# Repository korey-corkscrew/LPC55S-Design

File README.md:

# LPC55S-Design
## Flexcomm Assignment

## Schematics
### MCU

### EERAM

### Camera

### TOF

### WiFi

### CAN

### USB

### JTAG

## PCB

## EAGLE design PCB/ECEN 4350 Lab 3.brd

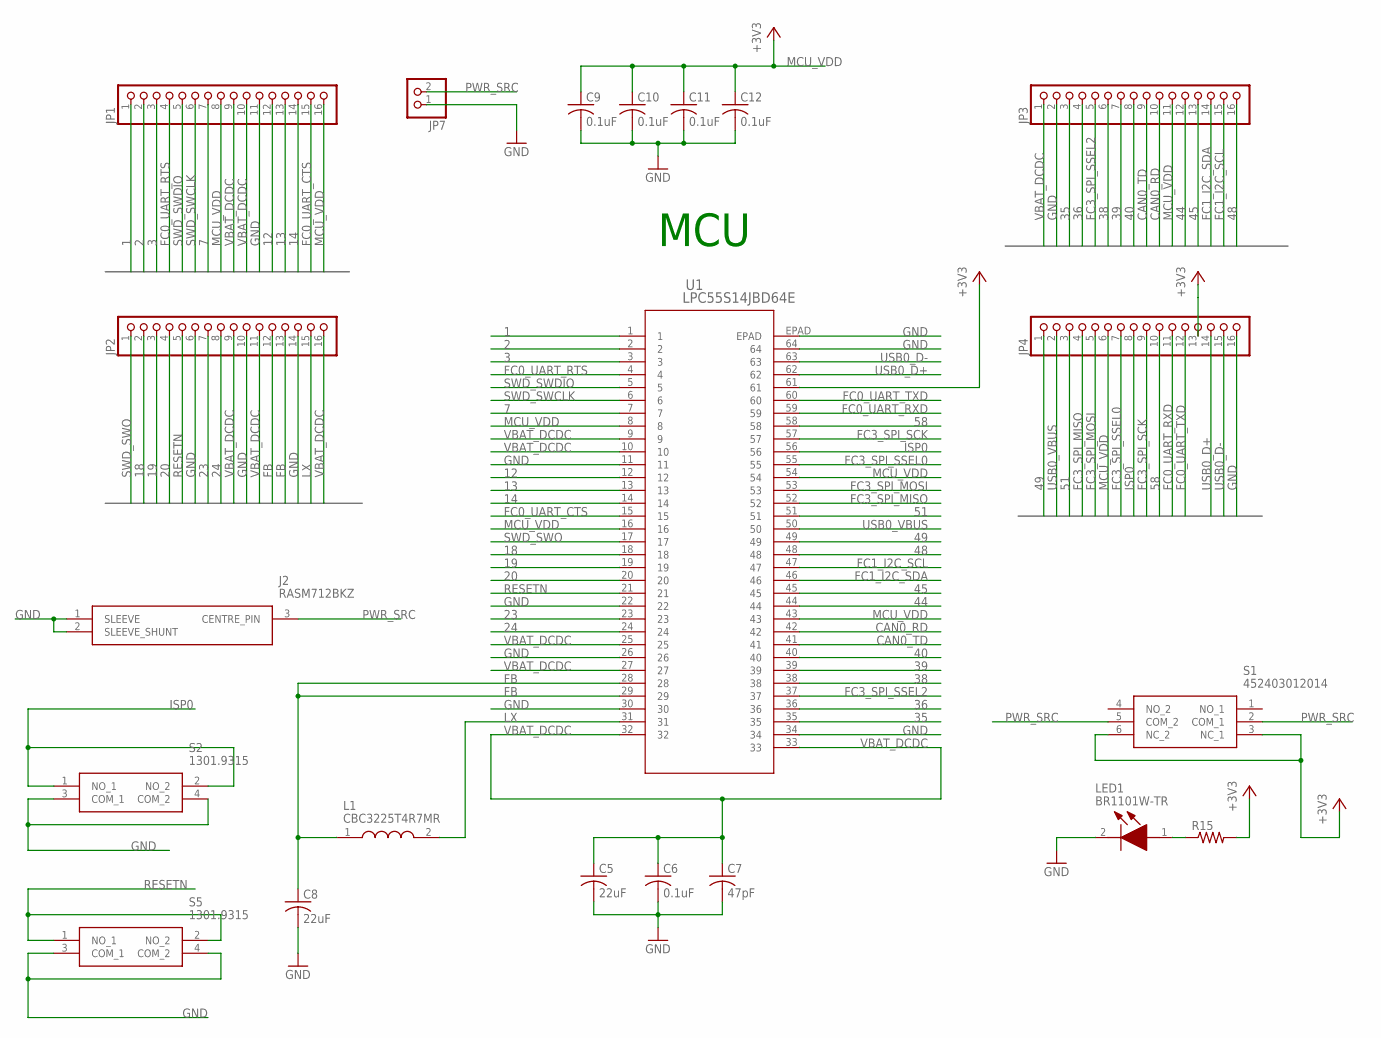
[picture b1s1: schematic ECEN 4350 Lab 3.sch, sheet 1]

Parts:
C5, C8: 22uF; C1206
C6, C9, C10, C11, C12: 0.1uF; C1206
C7: 47pF; C1206
J2: RASM712BKZ
JP1, JP2, JP3, JP4: PINHD-1X16; 1X16
JP7: PINHD-1X2; 1X02
L1: CBC3225T4R7MR; INDC3225X270N
LED1: BR1101W-TR; BR1101WTR
R15: R-US_R1206; R1206
S1: 452403012014
S2, S5: 1301.9315; 13019319
U1: LPC55S14JBD64E; HTQFP64_10X10_NXP

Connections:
1: JP1.1, U1.1
2: JP1.2, U1.2
3: JP1.3, U1.3
7: JP1.7, U1.7
12: JP1.12, U1.12
13: JP1.13, U1.13
14: JP1.14, U1.14
18: JP2.2, U1.18
19: JP2.3, U1.19
20: JP2.4, U1.20
23: JP2.7, U1.23
24: JP2.8, U1.24
35: JP3.3, U1.35
36: JP3.4, U1.36
38: JP3.6, U1.38
39: JP3.7, U1.39
40: JP3.8, U1.40
44: JP3.12, U1.44
45: JP3.13, U1.45
48: JP3.16, U1.48
49: JP4.1, U1.49
51: JP4.3, U1.51
58: JP4.10, U1.58
+3V3: R15.2, S1.3 (NC_1), S1.6 (NC_2), U1.61; also elsewhere on the board
CAN0_RD: JP3.10, U1.42; also elsewhere on the board
CAN0_TD: JP3.9, U1.41; also elsewhere on the board
FB: C8.1, JP2.12, JP2.13, L1.1, U1.28, U1.29
FC0_UART_CTS: JP1.15, U1.15
FC0_UART_RTS: JP1.4, U1.4
FC0_UART_RXD: JP4.11, U1.59; also elsewhere on the board
FC0_UART_TXD: JP4.12, U1.60; also elsewhere on the board
FC1_I2C_SCL: JP3.15, U1.47; also elsewhere on the board
FC1_I2C_SDA: JP3.14, U1.46; also elsewhere on the board
FC3_SPI_MISO: JP4.4, U1.52; also elsewhere on the board
FC3_SPI_MOSI: JP4.5, U1.53; also elsewhere on the board
FC3_SPI_SCK: JP4.9, U1.57; also elsewhere on the board
FC3_SPI_SSEL0: JP4.7, U1.55; also elsewhere on the board
FC3_SPI_SSEL2: JP3.5, U1.37; also elsewhere on the board
GND: C5.2, C6.2, C7.2, C8.2, C9.2, C10.2, C11.2, C12.2, J2.1 (SLEEVE), J2.2 (SLEEVE_SHUNT), JP1.11, JP2.6, JP2.10, JP2.14, JP3.2, JP4.16, JP7.1, LED1.2 (K), S2.3 (COM_1), S2.4 (COM_2), S5.3 (COM_1), S5.4 (COM_2), U1.11, U1.22, U1.26, U1.30, U1.34, U1.64, U1.EPAD; also elsewhere on the board
ISP0: JP4.8, S2.1 (NO_1), S2.2 (NO_2), U1.56
LX: JP2.15, L1.2, U1.31
MCU_VDD: C9.1, C10.1, C11.1, C12.1, JP1.8, JP1.16, JP3.11, JP4.6, U1.8, U1.16, U1.43, U1.54
unnamed: LED1.1 (A), R15.1
PWR_SRC: J2.3 (CENTRE_PIN), JP7.2, S1.2 (COM_1), S1.5 (COM_2)
RESETN: JP2.5, S5.1 (NO_1), S5.2 (NO_2), U1.21; also elsewhere on the board
SWD_SWCLK: JP1.6, U1.6; also elsewhere on the board
SWD_SWDIO: JP1.5, U1.5; also elsewhere on the board
SWD_SWO: JP2.1, U1.17; also elsewhere on the board
USB0_D+: JP4.14, U1.62; also elsewhere on the board
USB0_D-: JP4.15, U1.63; also elsewhere on the board
USB0_VBUS: JP4.2, U1.50; also elsewhere on the board
VBAT_DCDC: C5.1, C6.1, C7.1, JP1.9, JP1.10, JP2.9, JP2.11, JP2.16, JP3.1, U1.9, U1.10, U1.25, U1.27, U1.32, U1.33

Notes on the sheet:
MCU

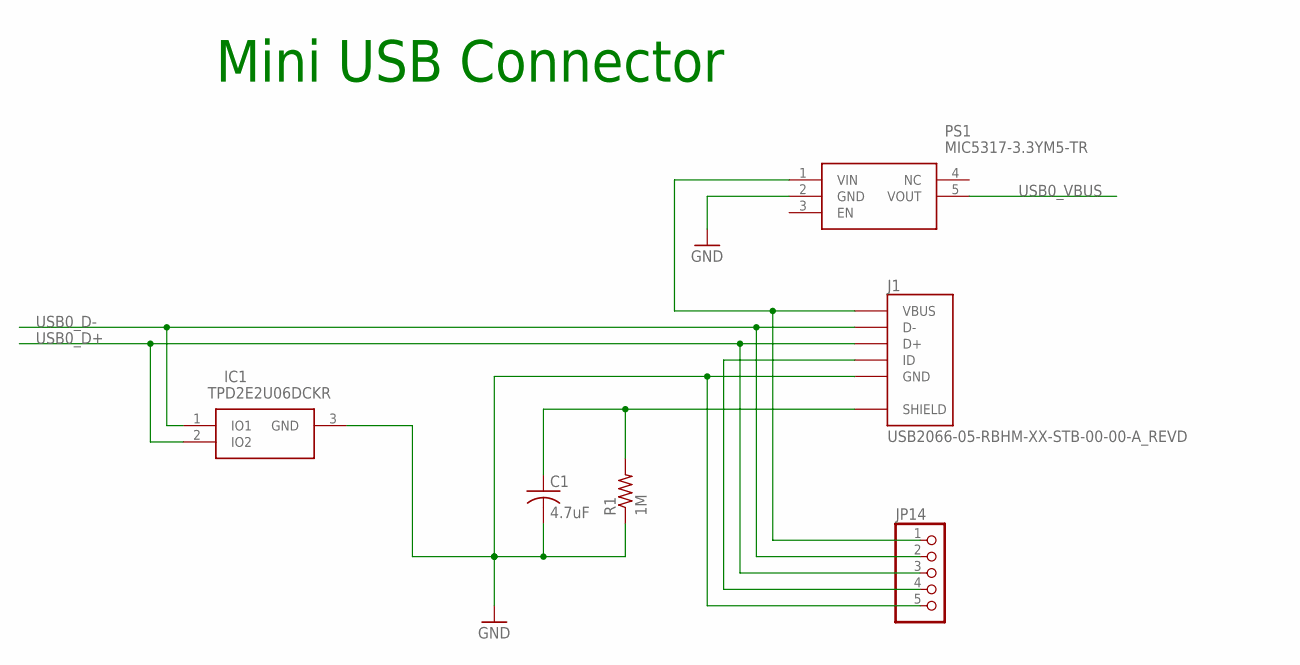
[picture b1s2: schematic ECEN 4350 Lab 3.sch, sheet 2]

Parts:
C1: 4.7uF; C1206
IC1: TPD2E2U06DCKR; SOT65P210X110-3N
J1: USB2066-05-RBHM-XX-STB-00-00-A_REVD; GCT_USB2066-05-RBHM-XX-STB-00-00-A_REVD
JP14: PINHD-1X5; 1X05
PS1: MIC5317-3.3YM5-TR; SOT95P280X100-5N
R1: 1M; R1206

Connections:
+5V: J1.1 (VBUS), JP14.1, PS1.1 (VIN)
GND: C1.2, IC1.3 (GND), J1.5 (GND), JP14.5, PS1.2 (GND), R1.1; also elsewhere on the board
unnamed: C1.1, J1.6 (SHIELD), J1.7 (SHIELD), J1.8 (SHIELD), J1.9 (SHIELD), R1.2
unnamed: J1.4 (ID), JP14.4
USB0_D+: IC1.2 (IO2), J1.3 (D+), JP14.3; also elsewhere on the board
USB0_D-: IC1.1 (IO1), J1.2 (D-), JP14.2; also elsewhere on the board
USB0_VBUS: PS1.5 (VOUT); also elsewhere on the board

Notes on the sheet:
Mini USB Connector

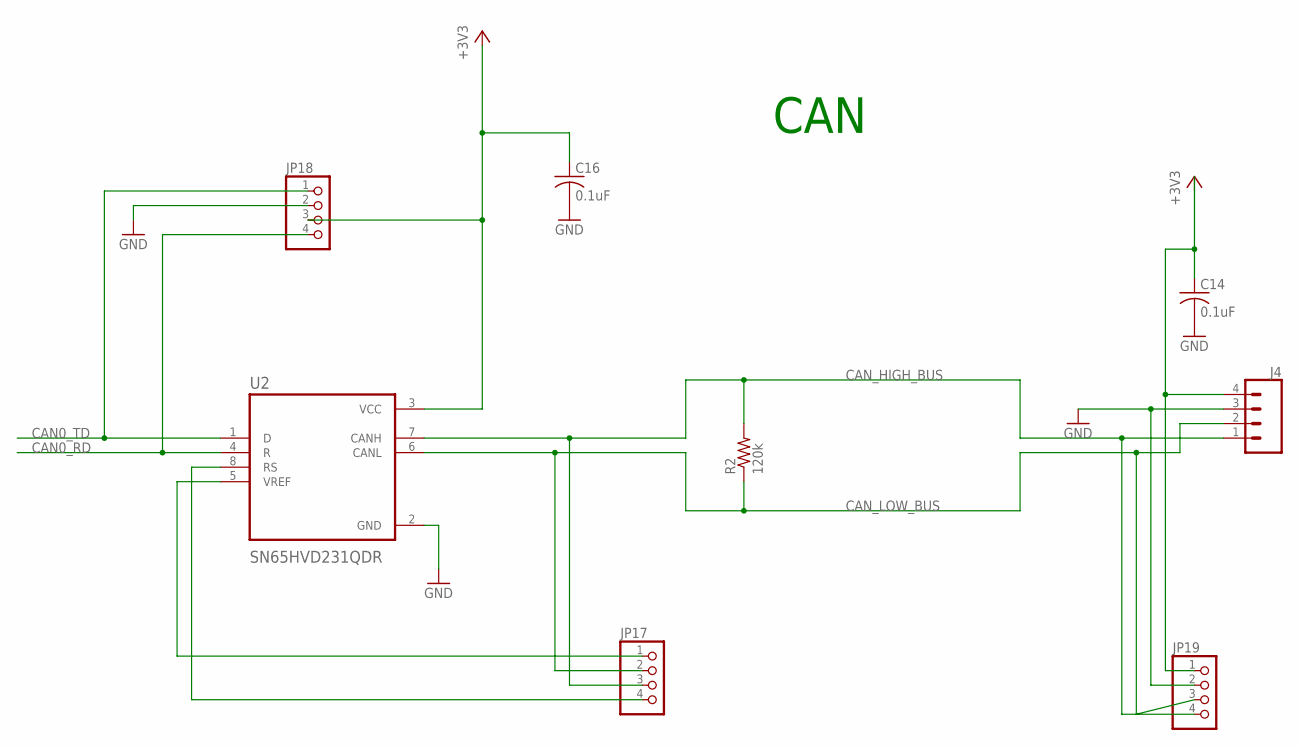
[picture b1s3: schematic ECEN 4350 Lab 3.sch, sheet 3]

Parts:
C14, C16: 0.1uF; C1206
J4: CONN_04SMD2; JST04_1MM_RA
JP17, JP18, JP19: PINHD-1X4; 1X04
R2: 120k; R1206
U2: SN65HVD231QDR; SOIC127P599X175-8N

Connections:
+3V3: C14.1, C16.1, J4.4, JP18.3, JP19.1, U2.3 (VCC); also elsewhere on the board
CAN0_RD: JP18.4, U2.4 (R); also elsewhere on the board
CAN0_TD: JP18.1, U2.1 (D); also elsewhere on the board
CAN_HIGH_BUS: J4.1, JP17.3, JP19.4, R2.2, U2.7 (CANH)
CAN_LOW_BUS: J4.2, JP17.2, JP19.3, R2.1, U2.6 (CANL)
GND: C14.2, C16.2, J4.3, JP18.2, JP19.2, U2.2 (GND); also elsewhere on the board
unnamed: JP17.4, U2.8 (RS)
unnamed: JP17.1, U2.5 (VREF)

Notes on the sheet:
CAN

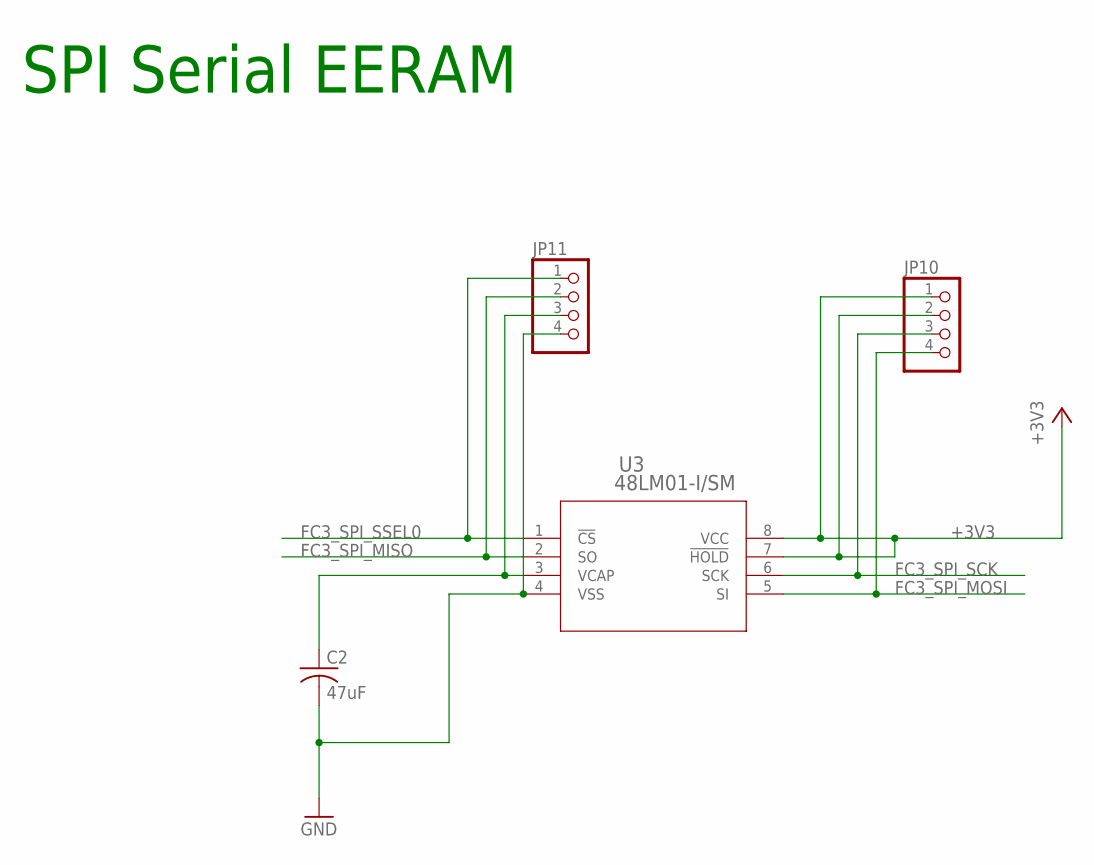
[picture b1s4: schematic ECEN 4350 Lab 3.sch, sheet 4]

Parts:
C2: 47uF; C1206
JP10, JP11: PINHD-1X4; 1X04
U3: 48LM01-I/SM; SOIJ8_SM_MCH

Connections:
+3V3: JP10.1, JP10.2, U3.7 (!HOLD), U3.8 (VCC); also elsewhere on the board
FC3_SPI_MISO: JP11.2, U3.2 (SO); also elsewhere on the board
FC3_SPI_MOSI: JP10.4, U3.5 (SI); also elsewhere on the board
FC3_SPI_SCK: JP10.3, U3.6 (SCK); also elsewhere on the board
FC3_SPI_SSEL0: JP11.1, U3.1 (!CS); also elsewhere on the board
GND: C2.2, JP11.4, U3.4 (VSS); also elsewhere on the board
unnamed: C2.1, JP11.3, U3.3 (VCAP)

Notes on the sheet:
SPI Serial EERAM

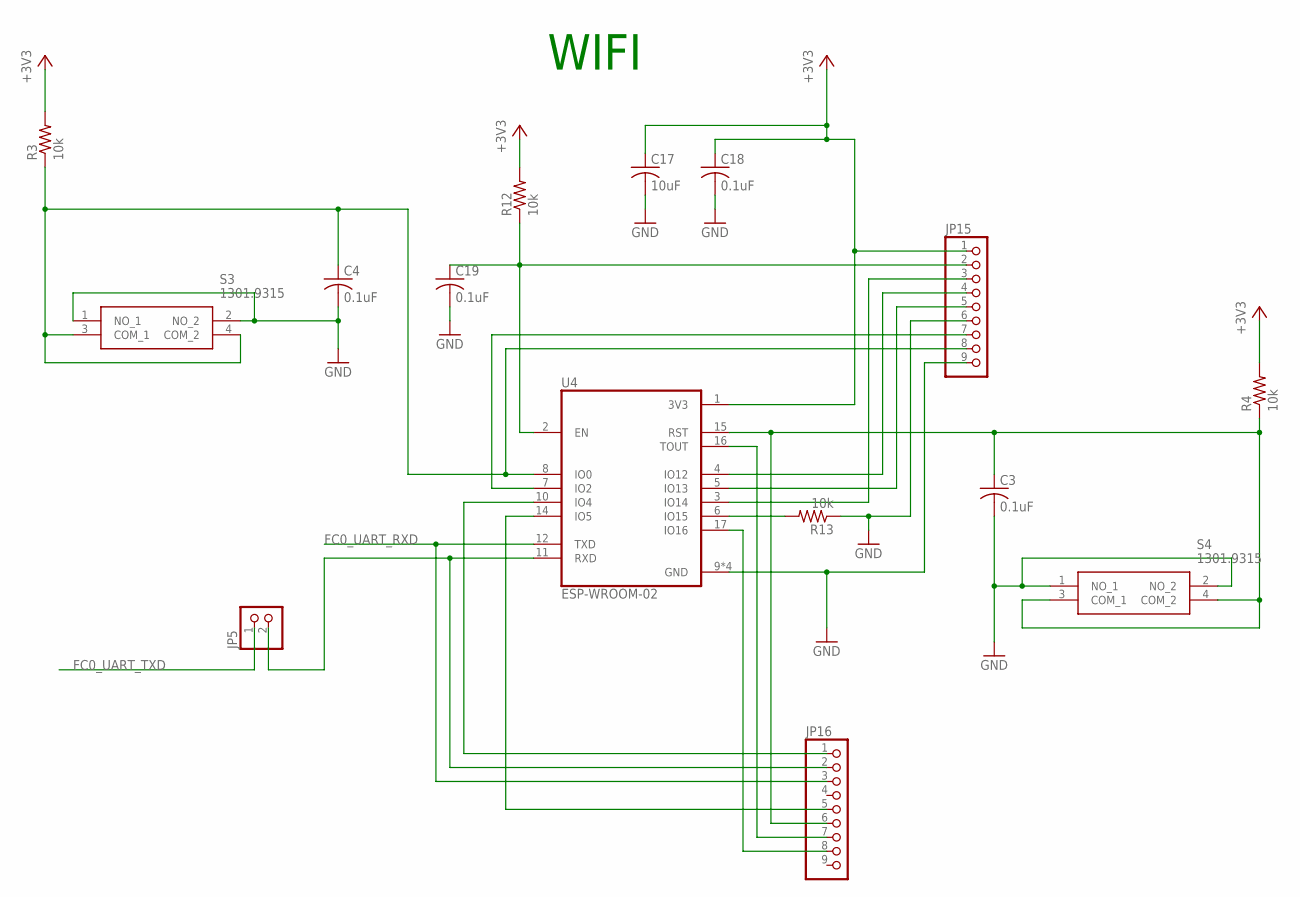
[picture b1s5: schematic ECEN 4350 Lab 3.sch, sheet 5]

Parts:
C3, C4, C18, C19: 0.1uF; C1206
C17: 10uF; C1206
JP5: PINHD-1X2; 1X02
JP15, JP16: PINHD-1X9; 1X09
R3, R4, R12, R13: 10k; M1206
S3, S4: 1301.9315; 13019319
U4: ESP-WROOM-02; MODULE_ESP-WROOM-02

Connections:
+3V3: C17.1, C18.1, JP15.1, R3.2, R4.2, R12.2, U4.1 (3V3); also elsewhere on the board
FC0_UART_RXD: JP16.3, U4.12 (TXD); also elsewhere on the board
FC0_UART_TXD: JP5.1; also elsewhere on the board
GND: C3.2, C4.2, C17.2, C18.2, C19.2, JP15.6, JP15.9, R13.1, S3.1 (NO_1), S3.2 (NO_2), S4.1 (NO_1), S4.2 (NO_2), U4.9 (GND), U4.13 (GND), U4.18 (GND), U4.19 (GND); also elsewhere on the board
unnamed: JP5.2, JP16.2, U4.11 (RXD)
unnamed: C4.1, JP15.8, R3.1, S3.3 (COM_1), S3.4 (COM_2), U4.8 (IO0)
unnamed: C19.1, JP15.2, R12.1, U4.2 (EN)
unnamed: JP15.3, U4.3 (IO14)
unnamed: C3.1, JP16.6, R4.1, S4.3 (COM_1), S4.4 (COM_2), U4.15 (RST)
unnamed: JP15.4, U4.4 (IO12)
unnamed: JP15.5, U4.5 (IO13)
unnamed: JP15.7, U4.7 (IO2)
unnamed: JP16.1, U4.10 (IO4)
unnamed: JP16.5, U4.14 (IO5)
unnamed: JP16.7, U4.16 (TOUT)
unnamed: JP16.8, U4.17 (IO16)
unnamed: R13.2, U4.6 (IO15)

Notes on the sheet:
WIFI

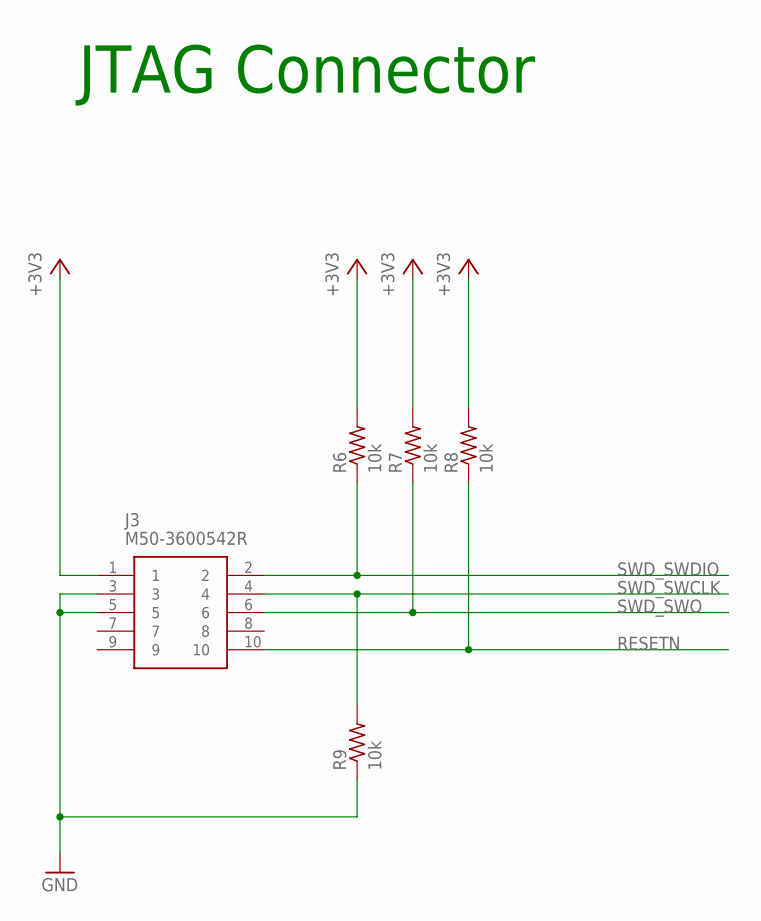
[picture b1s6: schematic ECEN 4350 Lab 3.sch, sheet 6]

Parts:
J3: M50-3600542R; HUSSP10W40P127_2X5_635X340X420
R6, R7, R8, R9: 10k; M1206

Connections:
+3V3: J3.1, R6.2, R7.2, R8.2; also elsewhere on the board
GND: J3.3, J3.5, R9.1; also elsewhere on the board
RESETN: J3.10, R8.1; also elsewhere on the board
SWD_SWCLK: J3.4, R9.2; also elsewhere on the board
SWD_SWDIO: J3.2, R6.1; also elsewhere on the board
SWD_SWO: J3.6, R7.1; also elsewhere on the board

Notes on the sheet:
JTAG Connector

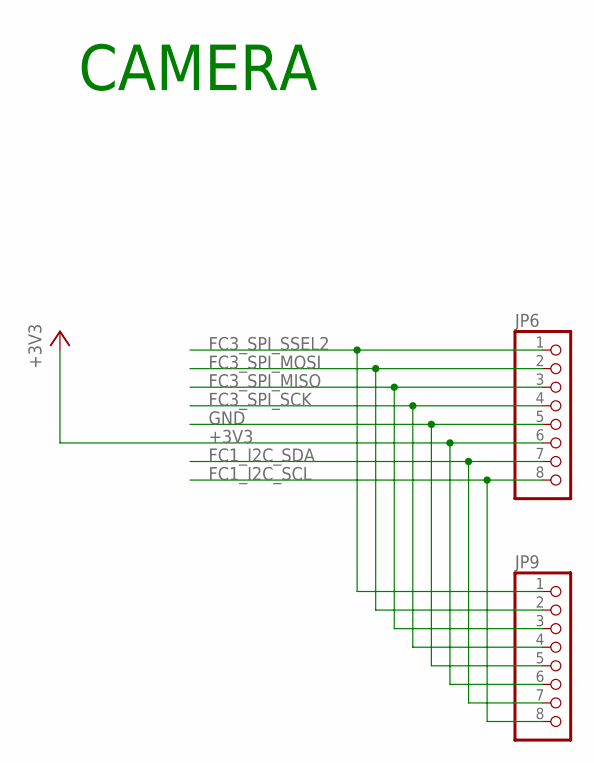
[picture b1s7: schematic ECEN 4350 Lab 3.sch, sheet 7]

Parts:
JP6, JP9: PINHD-1X8; 1X08

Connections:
+3V3: JP6.6, JP9.6; also elsewhere on the board
FC1_I2C_SCL: JP6.8, JP9.8; also elsewhere on the board
FC1_I2C_SDA: JP6.7, JP9.7; also elsewhere on the board
FC3_SPI_MISO: JP6.3, JP9.3; also elsewhere on the board
FC3_SPI_MOSI: JP6.2, JP9.2; also elsewhere on the board
FC3_SPI_SCK: JP6.4, JP9.4; also elsewhere on the board
FC3_SPI_SSEL2: JP6.1, JP9.1; also elsewhere on the board
GND: JP6.5, JP9.5; also elsewhere on the board

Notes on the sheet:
CAMERA

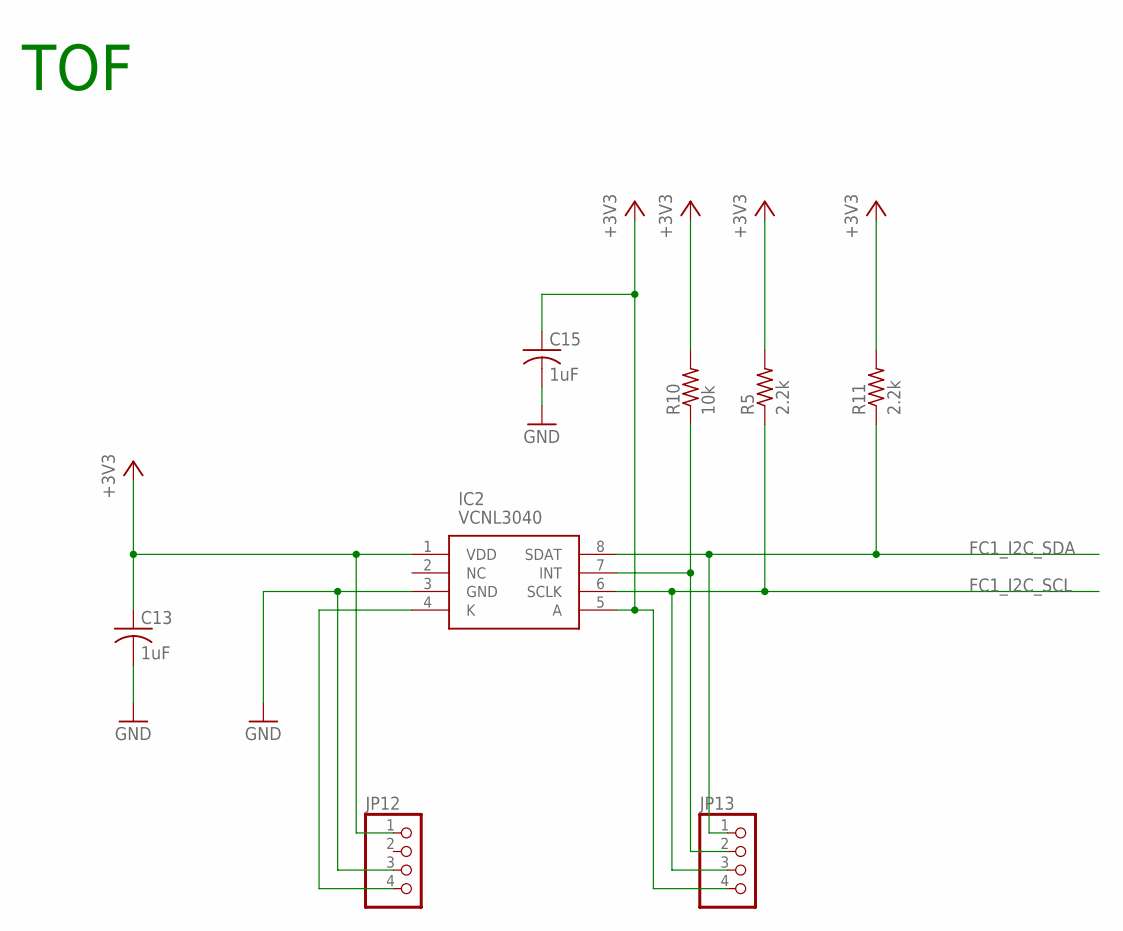
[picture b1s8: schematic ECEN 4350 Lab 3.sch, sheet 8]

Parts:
C13, C15: 1uF; C1206
IC2: VCNL3040; SON108P200X400X115-8N
JP12, JP13: PINHD-1X4; 1X04
R5, R11: 2.2k; M1206
R10: 10k; M1206

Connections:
+3V3: C13.1, C15.1, IC2.1 (VDD), IC2.5 (A), JP12.1, JP13.4, R5.2, R10.2, R11.2; also elsewhere on the board
FC1_I2C_SCL: IC2.6 (SCLK), JP13.3, R5.1; also elsewhere on the board
FC1_I2C_SDA: IC2.8 (SDAT), JP13.1, R11.1; also elsewhere on the board
GND: C13.2, C15.2, IC2.3 (GND), JP12.3; also elsewhere on the board
unnamed: IC2.7 (INT), JP13.2, R10.1
unnamed: IC2.4 (K), JP12.4

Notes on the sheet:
TOF

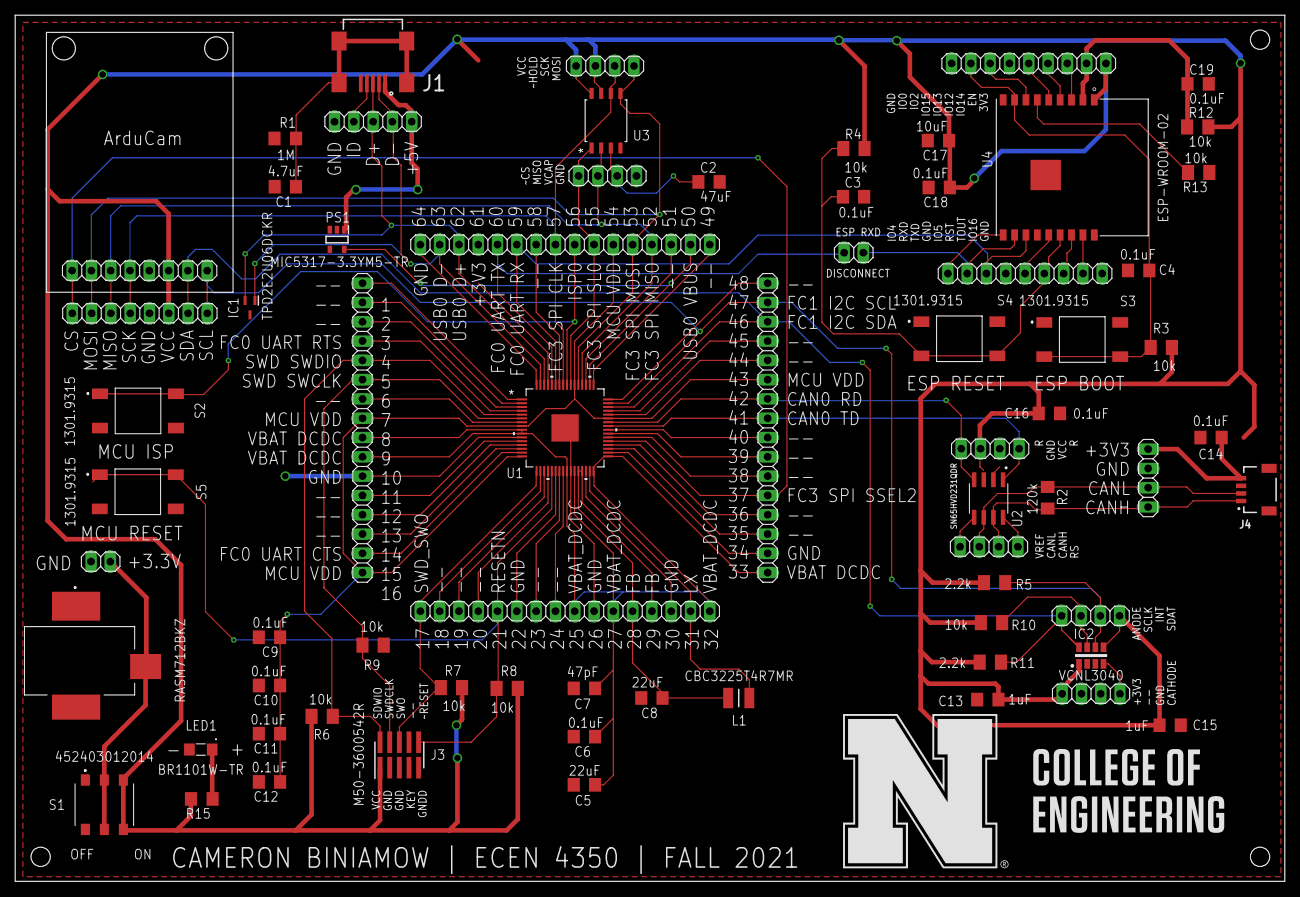
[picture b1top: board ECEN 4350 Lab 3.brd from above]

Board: 2 copper layers, 167.1 x 114.0 mm, 69 parts (0 on the bottom side), 75 nets.

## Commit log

2021-11-11 init

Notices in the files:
parts and their libraries:
SparkFun-Connectors: Licensing: Creative Commons ShareAlike 4.0 International - https://creativecommons.org/licenses/by-sa/4.0
COPYRIGHT: Copyright (C) 2021 Ultra Librarian. All rights reserved.
